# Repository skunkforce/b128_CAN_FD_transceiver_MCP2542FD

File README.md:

# edgy_board number b128
This design is part of the [edgy board project](https://github.com/skunkforce/edgy_boards).

# getting started
This repository uses submodules. After cloning use the command 

```$ git submodule update --init --recursive```

to pull the submodules before opening the project with kicad. 

# Tests
Tests can be found in [TESTS.md](TESTS.md)

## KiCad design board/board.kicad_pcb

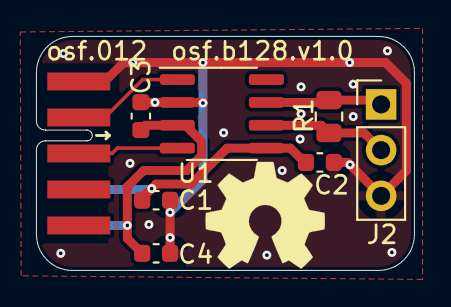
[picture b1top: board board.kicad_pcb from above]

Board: 2 copper layers, 21.0 x 13.0 mm, 9 parts (0 on the bottom side), 7 nets.

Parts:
C1, C2, C3, C4: 1uF; C_0603_1608Metric
J1: 012_CAN; on_edge_2x05_device
J2: Conn_01x03_Male; PinHeader_1x03_P2.54mm_Vertical
LOGO1: Logo_Open_Hardware_Small; OSHW-Symbol_6.7x6mm_SilkScreen
R1: 120R; R_0805_2012Metric
U1: MCP2542FDxMF; SOIC-8_3.9x4.9mm_P1.27mm

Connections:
/implementation/CANH: J2.1, R1.1, U1.7 (CANH)
/implementation/CANL: J2.2, R1.2, U1.6 (CANL)
/implementation/RX: J1.3 (RX), U1.4 (RXD)
/implementation/TX: J1.2 (TX), U1.1 (TXD)
/implementation/VDD: C3.1, C4.1, J1.10 (5V), U1.3 (VDD)
/implementation/VIO: C1.1, C2.1, J1.9 (3.3V), U1.5 (VIO)
GND: C1.2, C2.2, C3.2, C4.2, J1.1 (GND), J2.3, U1.2 (VSS)

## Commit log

2023-05-02 initial
2023-05-03 added render
2023-05-27 renamed subsheet to work better in compositions
